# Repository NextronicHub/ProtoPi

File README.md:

# Nextronic ProtoPi

The protoPi is a Raspberry pi prototyping shield with a small soldering area, LED, serial Pinout, SPI pinout, and i2c pinout with pull up resistance

##Repository Contents

/Hardware - Design files (.brd, .sch)  
/Documentation - datasheet and examples

##Product Versions

ProtoPi_V1 first release

##License Information

The hardware is released under [Creative Commons ShareAlike 4.0 International](https://creativecommons.org/licenses/by-sa/4.0/).

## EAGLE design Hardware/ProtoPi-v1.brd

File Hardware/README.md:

#  Nextronic ProtoPi Design Files

The .sch and .brd files are Eagle CAD schematic and PCB design files from Nextronic.
Eagle PCB Design | Schematic Editor, Layout Editor & Autorouter can be found at http://www.autodesk.com/products/eagle.

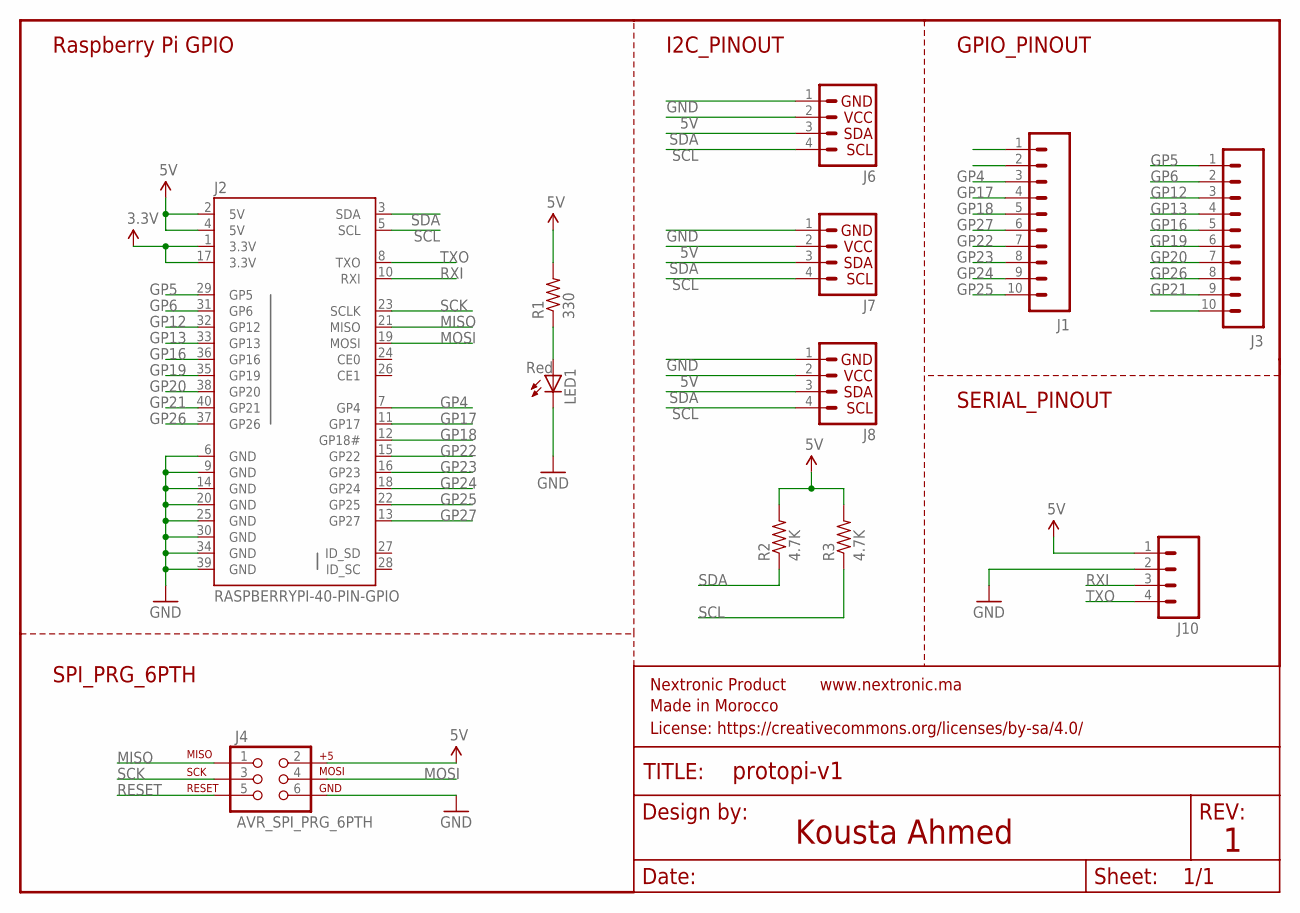
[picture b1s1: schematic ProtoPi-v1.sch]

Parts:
FRAME1: FRAME-LETTER; CREATIVE_COMMONS
J1, J3: M10SILK_FEMALE_PTH; 1X10
J2: RASPBERRYPI-40-PIN-GPIO; 2X20-SHROUDED
J4: AVR_SPI_PRG_6PTH; 2X3
J6, J7, J8: I2C_STANDARD; 1X04
J10: M04PTH; 1X04
LED1: Red; LED5MM
R1: 330; AXIAL-0.3
R2, R3: 4.7K; AXIAL-0.3

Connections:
3.3V: J2.1 (3.3V), J2.17 (3.3V)
5V: J2.2 (5V), J2.4 (5V), J4.2, J6.2, J7.2, J8.2, J10.1, R1.P$2 (2), R2.P$2 (2), R3.P$2 (2)
GND: J2.6 (GND), J2.9 (GND), J2.14 (GND), J2.20 (GND), J2.25 (GND), J2.30 (GND), J2.34 (GND), J2.39 (GND), J4.6, J6.1, J7.1, J8.1, J10.2, LED1.K (C)
GP4: J1.3, J2.7 (GP4)
GP5: J2.29 (GP5), J3.1
GP6: J2.31 (GP6), J3.2
GP12: J2.32 (GP12), J3.3
GP13: J2.33 (GP13), J3.4
GP16: J2.36 (GP16), J3.5
GP17: J1.4, J2.11 (GP17)
GP18: J1.5, J2.12 (GP18#)
GP19: J2.35 (GP19), J3.6
GP20: J2.38 (GP20), J3.7
GP21: J2.40 (GP21), J3.9
GP22: J1.7, J2.15 (GP22)
GP23: J1.8, J2.16 (GP23)
GP24: J1.9, J2.18 (GP24)
GP25: J1.10, J2.22 (GP25)
GP26: J2.37 (GP26), J3.8
GP27: J1.6, J2.13 (GP27)
MISO: J2.21 (MISO), J4.1
MOSI: J2.19 (MOSI), J4.4
unnamed: LED1.A, R1.P$1 (1)
RESET: J4.5
RXI: J2.10 (RXI), J10.3
SCK: J2.23 (SCLK), J4.3
SCL: J2.5 (SCL), J6.4, J7.4, J8.4, R3.P$1 (1)
SDA: J2.3 (SDA), J6.3, J7.3, J8.3, R2.P$1 (1)
TXO: J2.8 (TXO), J10.4

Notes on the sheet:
Kousta Ahmed
Raspberry Pi GPIO
SPI_PRG_6PTH
I2C_PINOUT
GPIO_PINOUT
SERIAL_PINOUT

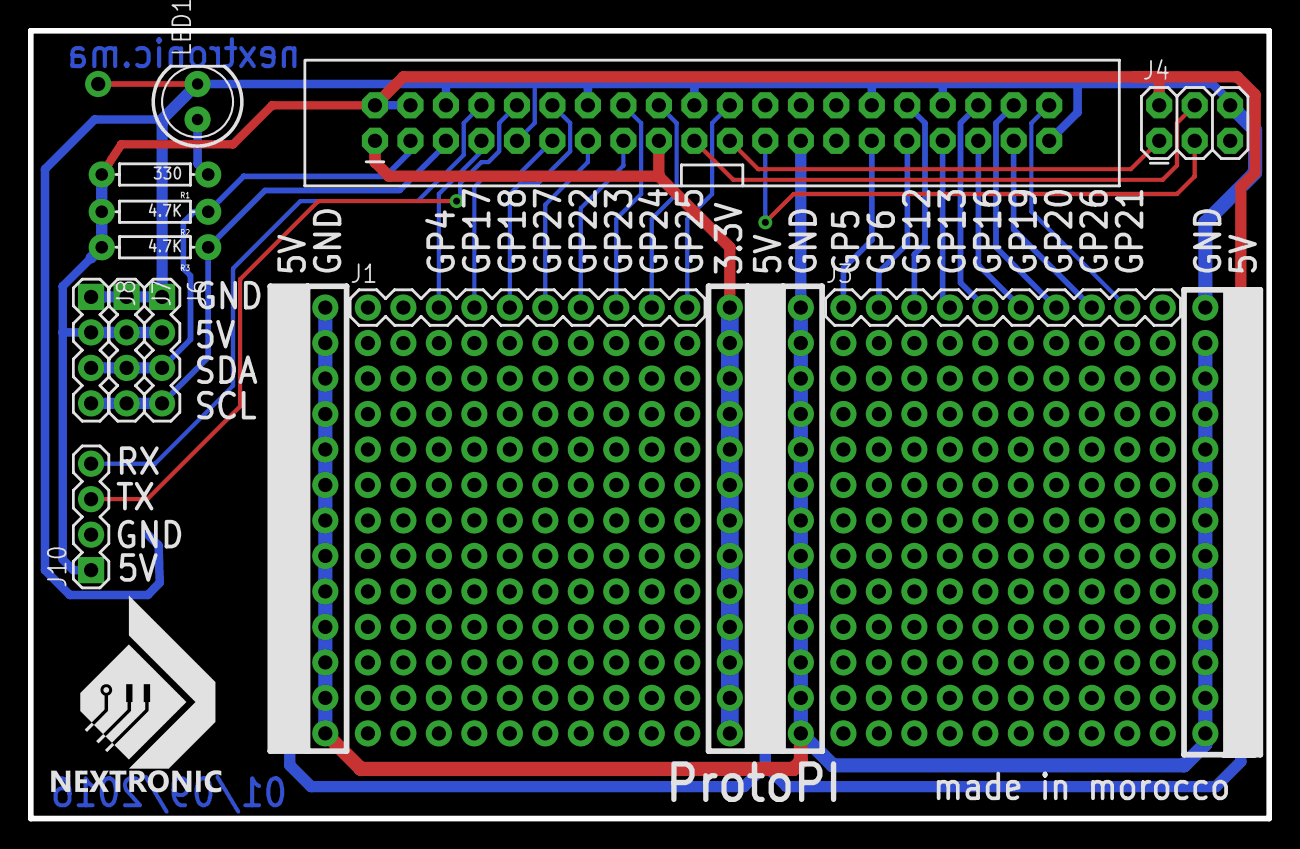
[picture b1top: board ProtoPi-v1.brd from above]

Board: 2 copper layers, 88.6 x 56.4 mm, 13 parts (0 on the bottom side), 28 nets.

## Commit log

2017-01-21 Create Hardware

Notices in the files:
parts and their libraries:
SparkFun-Boards: Licensing: Creative Commons ShareAlike 4.0 International - https://creativecommons.org/licenses/by-sa/4.0
SparkFun-Aesthetics: License: https://creativecommons.org/licenses/by-sa/4.0
